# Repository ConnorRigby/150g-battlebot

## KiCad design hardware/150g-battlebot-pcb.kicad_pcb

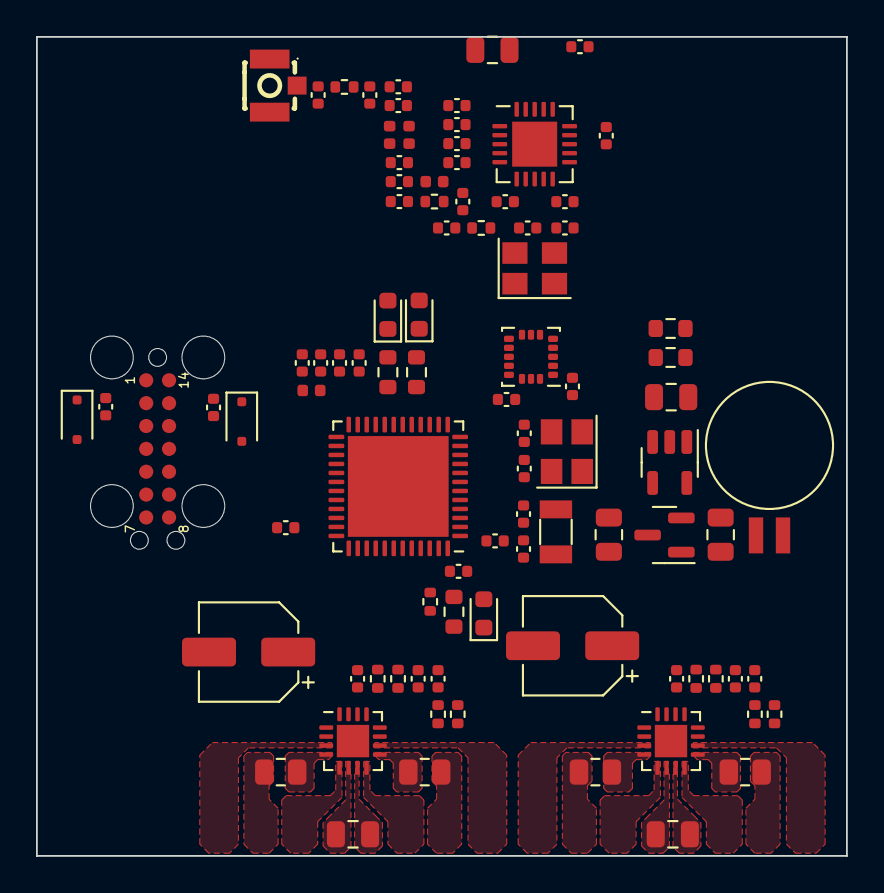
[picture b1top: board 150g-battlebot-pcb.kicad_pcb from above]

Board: 4 copper layers, 45.0 x 45.5 mm, 91 parts (0 on the bottom side), 67 nets, no tracks yet.

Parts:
AE201: Antenna_Chip; IPEX-SMD_BWIPX-1-001E
BT302: Battery_Cell; BatteryHolder_Seiko_MS621F
C201, C604, C606: C_805_DNP; C_0805_2012Metric
C202, C204: C_0402_2u2_X5R; C_0402_1005Metric
C203, C206, C207, C208, C209, C211, C214, C215, C216, C217, C218, C219, C220, C402, C403, C410, C411, C603, C609: C_0402_DNP; C_0402_1005Metric
C205, C401, C404, C405, C406, C407, C408, C409, C412, C501, C502: C_0402_100nf_X7R; C_0402_1005Metric
C210: C_0402_22p_C0G; C_0402_1005Metric
C212: C_0402_100p_C0G; C_0402_1005Metric
C213, C602, C608: C_0402_10n_C0G; C_0402_1005Metric
C301, C302: C_0805_1u_X7R; C_0805_2012Metric
C303: C_0805_4u7_X5R; C_0805_2012Metric
C304: C_0402_1u_X5R; C_0402_1005Metric
C601, C610: C_0402_1nf_X7R; C_0402_1005Metric
C605, C607: 2.2uF; CP_Elec_5x3
D301: BAT54C; SOT-23
D401, D402: 30v 230mv@100ma 1A; D_SOD-323F
D403, D404, D405: LED_0603_DNP; LED_0603_1608Metric
FB301: FerriteBead_Small; L_0402_1005Metric
J401: Conn_ST_STDC14; TC2070-IDC-FP
L202, L203, L204: L_0402_DNP; L_0402_1005Metric
R201, R203: DNP; R_0402_1005Metric
R202: 200; R_0402_1005Metric
R401, R605, R610: R_0402_1k; R_0402_1005Metric
R402, R403, R404, R501, R502: R_0603_DNP; R_0603_1608Metric
R601, R612: 18k; R_0402_1005Metric
R602, R603, R607, R609: 330M; R_0805_2012Metric
R604, R608: 39k; R_0402_1005Metric
R606, R611: 47k; R_0402_1005Metric
U103: A7105; QFN-20-1EP_4x4mm_P0.5mm_EP2.5x2.5mm
U301: MIC5504-3.3YM5; SOT-23-5
U401: STM32G431C6Ux; QFN-48-1EP_7x7mm_P0.5mm_EP5.6x5.6mm
U501: LIS3DH; LGA-16_3x3mm_P0.5mm_LayoutBorder3x5y
U601, U602: STSPIN240; VQFN-16-1EP_3x3mm_P0.5mm_EP1.8x1.8mm
Y201, Y401: 16_mhz; Crystal_SMD_3225-4Pin_3.2x2.5mm
Y402: Q13FC1350000400; Crystal_SMD_3215-2Pin_3.2x1.5mm

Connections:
+BATT: C303.1, C404.1, D301.3, U401.1 (VBAT)
/Application/BAT_SENSE: R501.1, R502.2, U401.45 (PB7)
/Application/BOOT0: R401.2, U401.46 (PB8)
/Application/FAULT: C602.1, C608.1, R604.2, R608.2, U401.2 (PC13), U601.13 (EN/FLT), U602.13 (EN/FLT)
/Application/IMU_INT1: U401.10 (PA2), U501.11 (INT1)
/Application/IMU_INT2: U401.11 (PA3), U501.9 (INT2)
/Application/JTCK: J401.6 (JCLK/SWCLK), U401.37 (PA14)
/Application/JTDI: J401.10 (JTDI/NC), U401.38 (PA15)
/Application/JTDO: J401.8 (JTDO/SWO), U401.41 (PB3)
/Application/JTMS: J401.4 (JTMS/SWDIO), U401.36 (PA13)
/Application/JTRST: C412.1, D402.2 (A), J401.12 (~RST)
/Application/M1_DIR: U401.26 (PB13), U601.2 (PWMA)
/Application/M1_PWM: U401.32 (PA10), U601.1 (PHA)
/Application/M2_DIR: U401.25 (PB12), U601.15 (PHB)
/Application/M2_PWM: U401.33 (PA11), U601.16 (PWMB)
/Application/M3_DIR: U401.39 (PC10), U602.1 (PHA)
/Application/M3_PWM: U401.27 (PB14), U602.2 (PWMA)
/Application/M4_DIR: U401.40 (PC11), U602.15 (PHB)
/Application/M4_PWM: U401.28 (PB15), U602.16 (PWMB)
/Application/OSC32_IN: C410.1, U401.3 (PC14), Y402.1
/Application/OSC32_OUT: C411.1, U401.4 (PC15), Y402.2
/Application/OSC_IN: C402.1, U401.5 (PF0), Y401.1
/Application/OSC_OUT: C403.1, U401.6 (PF1), Y401.3
/Application/REF: U401.29 (PC6), U601.11 (REF), U602.11 (REF)
/Application/RF_GIO2: U103.17 (GIO2), U401.17 (PB0)
/Application/SPI1_MISO: U103.16 (GIO1), U401.14 (PA6), U501.7 (SDO/SA0)
/Application/SPI1_MOSI: U103.14 (SDIO), U401.15 (PA7), U501.6 (SDA/SDI/SDO)
/Application/SPI1_SCK: U103.12 (SCK), U401.13 (PA5), U501.4 (SCL/SPC)
/Application/STATUS1: R402.1, U401.47 (PB9)
/Application/STATUS1_CLR: D403.1 (K), R402.2
/Application/STATUS2: R403.1, U401.18 (PB1)
/Application/STATUS2_CLR: D404.1 (K), R403.2
/Application/STATUS3: R404.1, U401.19 (PB2)
/Application/STATUS3_CLR: D405.1 (K), R404.2
/Application/VCP_RX: J401.14 (VCP_TX), U401.24 (PB11)
/Application/VCP_TX: J401.13 (VCP_RX), U401.22 (PB10)
/Application/~IMU_CS: U401.12 (PA4), U501.8 (CS)
/Application/~RESET: C601.1, C610.1, D402.1 (K), R601.2, R612.2, U401.7 (PG10), U601.14 (STBY/RESET), U602.14 (STBY/RESET)
/Application/~RF_CS: U103.11 (SCS), U401.16 (PC4)
/MotorDrivers/M1_M2_TOFF: R605.1, R606.1, U601.12 (TOFF)
/MotorDrivers/M1_SENSE: R602.1, U601.4 (SENSEA)
/MotorDrivers/M2_SENSE: R603.1, U601.9 (SENSEB)
/MotorDrivers/M3_M4_TOFF: R610.1, R611.1, U602.12 (TOFF)
/MotorDrivers/M3_SENSE: R607.1, U602.4 (SENSEA)
/MotorDrivers/M4_SENSE: R609.1, U602.9 (SENSEB)
/PowerInput/VIN: C301.1, U301.1 (VIN), U301.3 (EN)
/RF/ANT: C217.1, C218.1, C220.2, L204.1, R203.1
/RF/BPBG: C208.2, U103.2 (BPBG)
/RF/REG0A: C201.1, C205.1, C211.2, C212.1, L203.2, R201.1, U103.10 (VDA3), U103.20 (VDA1)
/RF/RFI: C210.2, U103.3 (RFI)
/RF/RFO: C206.1, L203.1, U103.4 (RFO)
/RF/RSSI: C207.2, U103.1 (RSSI)
/RF/VDA2: C203.2, R201.2, U103.5 (VDA2)
GND: AE201.2 (PCB_Trace), BT302.2 (-), C201.2, C202.2, C203.1, C204.2, C205.2, C207.1, C208.1, C209.1, C211.1, C212.2, C213.1, C214.2, C215.2, C216.2, C217.2, C218.2, C219.1, C220.1, C301.2, C302.2, C303.2, C304.2, C401.2, C402.2, C403.2, C404.2, C405.2, C406.2, C407.2, C408.2, C409.2, C410.2, C411.2, C412.2, C501.2, C502.2, C601.2, C602.2, C603.2, C604.2, C605.2, C606.2, C607.2, C608.2, C609.2, C610.2, J401.5 (GND), J401.7 (GND), J401.11 (GNDDetect), L202.1, R501.2, R602.2, R603.2, R606.2, R607.2, R609.2, R611.2, U103.7 (GND), U103.15 (GND), U103.21 (EP), U301.2 (GND), U401.49 (VSS), U501.5 (GND), U501.10 (GND), U501.12 (GND), U501.13 (ADC3), U501.15 (ADC2), U501.16 (ADC1), U601.7 (GND), U601.17 (EPAD), U602.7 (GND), U602.17 (EPAD), Y201.2, Y201.4, Y401.2, Y401.4
unnamed: AE201.1 (FEED), C219.2, R203.2
unnamed: BT302.1 (+), D301.1
unnamed: C206.2, C210.1, C216.1, L202.2, L204.2
unnamed: C213.2, R202.1
unnamed: C603.1, R605.2
unnamed: C609.1, R610.2
unnamed: C401.1, D401.1 (K), J401.3 (VCC)
unnamed: C209.2, R202.2, U103.6 (VT)
unnamed: C215.1, U103.8 (XI), Y201.1
unnamed: C214.1, U103.9 (XO), Y201.3
VDD: C202.1, C204.1, C302.1, C405.1, C406.1, C407.1, C501.1, C502.1, D301.2, D401.2 (A), D403.2 (A), D404.2 (A), D405.2 (A), FB301.1, R401.1, R601.1, R604.1, R608.1, R612.1, U103.13 (DVDD), U103.19 (REGI), U301.5 (VOUT), U401.23 (VDD), U401.35 (VDD), U401.48 (VDD), U501.1 (VDD_IO), U501.14 (VDD)
VDDA: C304.1, C408.1, C409.1, FB301.2, U401.20 (VREF+), U401.21 (VDDA)
VS: C604.1, C605.1, C606.1, C607.1, R502.1, U601.6 (VS), U602.6 (VS)

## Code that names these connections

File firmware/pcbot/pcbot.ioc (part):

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PB13.GPIOParameters=GPIO_Label
PA6.Mode=Full_Duplex_Master
Mcu.UserName=STM32G431C6Ux
PB10.Mode=Asynchronous
PC10.Signal=GPIO_Output
PB14.GPIO_Label=M3_PWM
PA0.GPIO_Label=M2_ENCA
PA12.GPIOParameters=GPIO_Label
PA9.GPIOParameters=GPIO_Label
PA11.GPIOParameters=GPIO_Label
PC6.GPIO_Label=REF
PG10-NRST.GPIO_Label=RESET
PA3.GPIOParameters=GPIO_Label
PB0.GPIO_Label=RF_INT
PB6.GPIO_Label=M4_ENCA
PC13.GPIO_Label=FAULT
PB13.GPIO_Label=M1_DIR
PB11.Signal=USART3_RX
PB13.Signal=GPIO_Output
PB15.Signal=S_TIM15_CH2
PA2.GPIOParameters=GPIO_Label
PB5.GPIOParameters=GPIO_Label
PB4.GPIOParameters=GPIO_Label
PA12.Signal=S_TIM4_CH2
PB6.Signal=S_TIM4_CH1
PA8.GPIOParameters=GPIO_Label
RCC.HSE_VALUE=8000000
PB3.Mode=JTAG_4_pins
PA15.Mode=JTAG_4_pins
PB12.GPIO_Label=M2_DIR
PB0.GPIOParameters=GPIO_Label
PA1.GPIOParameters=GPIO_Label
PC14-OSC32_IN.Mode=LSE-External-Oscillator
PC4.GPIO_Label=RF_CS
PA14.Mode=JTAG_4_pins
PC11.GPIO_Label=M4_DIR
PA10.GPIO_Label=M2_PWM
PB7.Signal=SharedAnalog_PB7
PA8.Signal=S_TIM1_CH1
PB6.GPIOParameters=GPIO_Label
PA0.Signal=S_TIM2_CH1
PB7.GPIO_Label=BAT_SENSE
Mcu.Package=UFQFPN48
PB9.Signal=S_TIM8_CH3
PA6.Signal=SPI1_MISO
PA2.GPIO_Label=IMU_INT1
PA10.Signal=S_TIM1_CH3
PA15.Signal=SYS_JTDI
PB14.GPIOParameters=GPIO_Label
PB5.GPIO_Label=M3_ENCB
PB10.GPIOParameters=GPIO_Label
PF1-OSC_OUT.Mode=HSE-External-Oscillator
PA4.GPIO_Label=IMU_CS
PC4.GPIOParameters=GPIO_Label
PF1-OSC_OUT.Signal=RCC_OSC_OUT
PB4.Signal=S_TIM3_CH1
PA3.Signal=GPXTI3
PA5.Mode=Full_Duplex_Master
PC15-OSC32_OUT.Mode=LSE-External-Oscillator
PA7.Mode=Full_Duplex_Master
PC10.GPIO_Label=M3_DIR
PA9.GPIO_Label=M1_ENCB
PC13.Signal=GPIO_Input
PC11.Signal=GPIO_Output
PC4.Signal=GPIO_Output
PC6.Signal=S_TIM8_CH1
PB11.GPIO_Label=VCP_RX
PA11.GPIO_Label=M1_PWM
PC14-OSC32_IN.Signal=RCC_OSC32_IN
PC11.GPIOParameters=GPIO_Label
PA12.GPIO_Label=M4_ENCB
PA13.Signal=SYS_JTMS-SWDIO
PA8.GPIO_Label=M1_ENCA
PB11.Mode=Asynchronous
PG10-NRST.Signal=GPIO_Output
PB10.GPIO_Label=VCP_TX
PB7.GPIOParameters=GPIO_Label
PA9.Signal=S_TIM1_CH2
PB11.GPIOParameters=GPIO_Label
PC15-OSC32_OUT.Signal=RCC_OSC32_OUT
PA1.Signal=S_TIM2_CH2
PF0-OSC_IN.Mode=HSE-External-Oscillator
PB10.Signal=USART3_TX
PB14.Signal=S_TIM15_CH1
PA5.Signal=SPI1_SCK
PB8-BOOT0.Signal=GPIO_Input
board=custom
PB4.GPIO_Label=M3_ENCA
PB15.GPIO_Label=M4_PWM
PC13.GPIOParameters=GPIO_Label
PA1.GPIO_Label=M2_ENCB
PA10.GPIOParameters=GPIO_Label
PA4.GPIOParameters=GPIO_Label
PC10.GPIOParameters=GPIO_Label
PB15.GPIOParameters=GPIO_Label
PA13.Mode=JTAG_4_pins
Mcu.Name=STM32G431C(6-8-B)Ux
PA2.Signal=SYS_WKUP4
PB3.Signal=SYS_JTDO-SWO
PA4.Signal=GPIO_Output
RCC.SYSCLKFreq_VALUE=16000000
PB5.Signal=S_TIM3_CH2
PA11.Signal=S_TIM1_CH4
PA14.Signal=SYS_JTCK-SWCLK
PA0.GPIOParameters=GPIO_Label
PC6.GPIOParameters=GPIO_Label
PG10-NRST.GPIOParameters=GPIO_Label
PA2.Mode=SYS_WakeUp3
PF0-OSC_IN.Signal=RCC_OSC_IN
PB0.Signal=GPXTI0
PB12.GPIOParameters=GPIO_Label
PB12.Signal=GPIO_Output
PA3.GPIO_Label=IMU_INT2
PA7.Signal=SPI1_MOSI

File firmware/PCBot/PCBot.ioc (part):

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Mcu.Name=STM32G431C(6-8-B)Ux
Mcu.Package=UFQFPN48
Mcu.UserName=STM32G431CBUx
PA0.GPIOParameters=GPIO_Label
PA0.GPIO_Label=RADIO_IRQ
PA0.Mode=SYS_WakeUp0
PA0.Signal=SYS_WKUP1
PA1.GPIOParameters=GPIO_Label
PA1.GPIO_Label=M2_PWM
PA1.Signal=S_TIM2_CH2
PA10.GPIOParameters=GPIO_Label
PA10.GPIO_Label=M1_DIR
PA10.Signal=GPIO_Output
PA11.GPIOParameters=GPIO_Label
PA11.GPIO_Label=VBAT_STATUS
PA11.Mode=ExternalOutput
PA11.Signal=COMP1_OUT
PA12.GPIOParameters=GPIO_Label
PA12.GPIO_Label=M2_DIR
PA12.Signal=GPIO_Output
PA13.Mode=JTAG_5_pins
PA13.Signal=SYS_JTMS-SWDIO
PA14.Mode=JTAG_5_pins
PA14.Signal=SYS_JTCK-SWCLK
PA15.Mode=JTAG_5_pins
PA15.Signal=SYS_JTDI
PA2.GPIOParameters=GPIO_Label
PA2.GPIO_Label=IMU_IRQ2
PA2.Mode=SYS_WakeUp3
PA2.Signal=SYS_WKUP4
PA3.Mode=Follower_Internally_Connected
PA3.Signal=OPAMP1_VINP
PA4.GPIOParameters=GPIO_Label
PA4.GPIO_Label=M2_REF
PA4.Signal=S_TIM3_CH2
PA5.GPIOParameters=GPIO_Label
PA5.GPIO_Label=M1_PWM
PA5.Signal=S_TIM2_CH1
PA6.GPIOParameters=GPIO_Label
PA6.GPIO_Label=M1_REF
PA6.Signal=S_TIM3_CH1
PA7.GPIOParameters=GPIO_Label
PA7.GPIO_Label=M1_SENSE
PA7.Mode=PGA_Internally_Connected
PA7.Signal=OPAMP2_VINP
PA8.GPIOParameters=GPIO_Label
PA8.GPIO_Label=M1_ENCA
PA8.Signal=S_TIM1_CH1
PA9.GPIOParameters=GPIO_Label
PA9.GPIO_Label=M1_ENCB
PA9.Signal=S_TIM1_CH2
PB0.GPIOParameters=GPIO_Label
PB0.GPIO_Label=M2_SENSE
PB0.Mode=PGA_Internally_Connected
PB0.Signal=OPAMP3_VINP
PB1.GPIOParameters=GPIO_Label
PB1.GPIO_Label=VBAT_SENSE
PB1.Mode=INP
PB1.Signal=COMP1_INP
PB10.Mode=Asynchronous
PB10.Signal=LPUART1_RX
PB11.Mode=Asynchronous
PB11.Signal=LPUART1_TX
PB12.Mode=NSS_Signal_Hard_Output
PB12.Signal=SPI2_NSS
PB13.Mode=Full_Duplex_Master
PB13.Signal=SPI2_SCK
PB14.Mode=Full_Duplex_Master
PB14.Signal=SPI2_MISO
PB15.Mode=Full_Duplex_Master
PB15.Signal=SPI2_MOSI
PB3.Mode=JTAG_5_pins
PB3.Signal=SYS_JTDO-SWO
PB4.Mode=JTAG_5_pins
PB4.Signal=SYS_JTRST
PB5.Mode=Full_Duplex_Master
PB5.Signal=SPI3_MOSI
PB8-BOOT0.GPIOParameters=GPIO_Label
PB8-BOOT0.GPIO_Label=M2_ENCB
PB8-BOOT0.Signal=S_TIM8_CH2
PC10.Mode=Full_Duplex_Master
PC10.Signal=SPI3_SCK
PC11.Mode=Full_Duplex_Master
PC11.Signal=SPI3_MISO
PC13.GPIOParameters=GPIO_Label
PC13.GPIO_Label=IMU_IRQ1
PC13.Mode=SYS_WakeUp1
PC13.Signal=SYS_WKUP2
PC14-OSC32_IN.Mode=LSE-External-Oscillator
PC14-OSC32_IN.Signal=RCC_OSC32_IN
PC15-OSC32_OUT.Mode=LSE-External-Oscillator
PC15-OSC32_OUT.Signal=RCC_OSC32_OUT
PC6.GPIOParameters=GPIO_Label
PC6.GPIO_Label=M2_ENCA
PC6.Signal=S_TIM8_CH1
PF0-OSC_IN.Mode=HSE-External-Oscillator
PF0-OSC_IN.Signal=RCC_OSC_IN
PF1-OSC_OUT.Mode=HSE-External-Oscillator
PF1-OSC_OUT.Signal=RCC_OSC_OUT
PG10-NRST.GPIOParameters=GPIO_Label
PG10-NRST.GPIO_Label=MC_RESET
PG10-NRST.Signal=GPIO_Output
RCC.HSE_VALUE=16000000
RCC.SYSCLKFreq_VALUE=16000000
board=custom

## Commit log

2023-05-22 initial commit 2
2023-05-23 initial commit 3
2023-05-23 initial commit 4
2023-05-24 initial commit 6
2023-05-25 intiial commit uhhhhh
2023-05-25 uhhhhhhhhhhhhhhhhhhhhhhhh
2023-05-26 initial commit 69
2023-05-26 initial commit 420
2023-06-01 womp Signed-off-by: Connor Rigby <connorr@hey.com>
2023-06-02 i uhhhhhhhhhhhhhhhhhhhhh
2023-06-09 sdfasdfa
2023-06-09 asdf
2023-06-10 checkpoint
2023-06-13 sdfasdf
2023-06-14 pcb initialize
